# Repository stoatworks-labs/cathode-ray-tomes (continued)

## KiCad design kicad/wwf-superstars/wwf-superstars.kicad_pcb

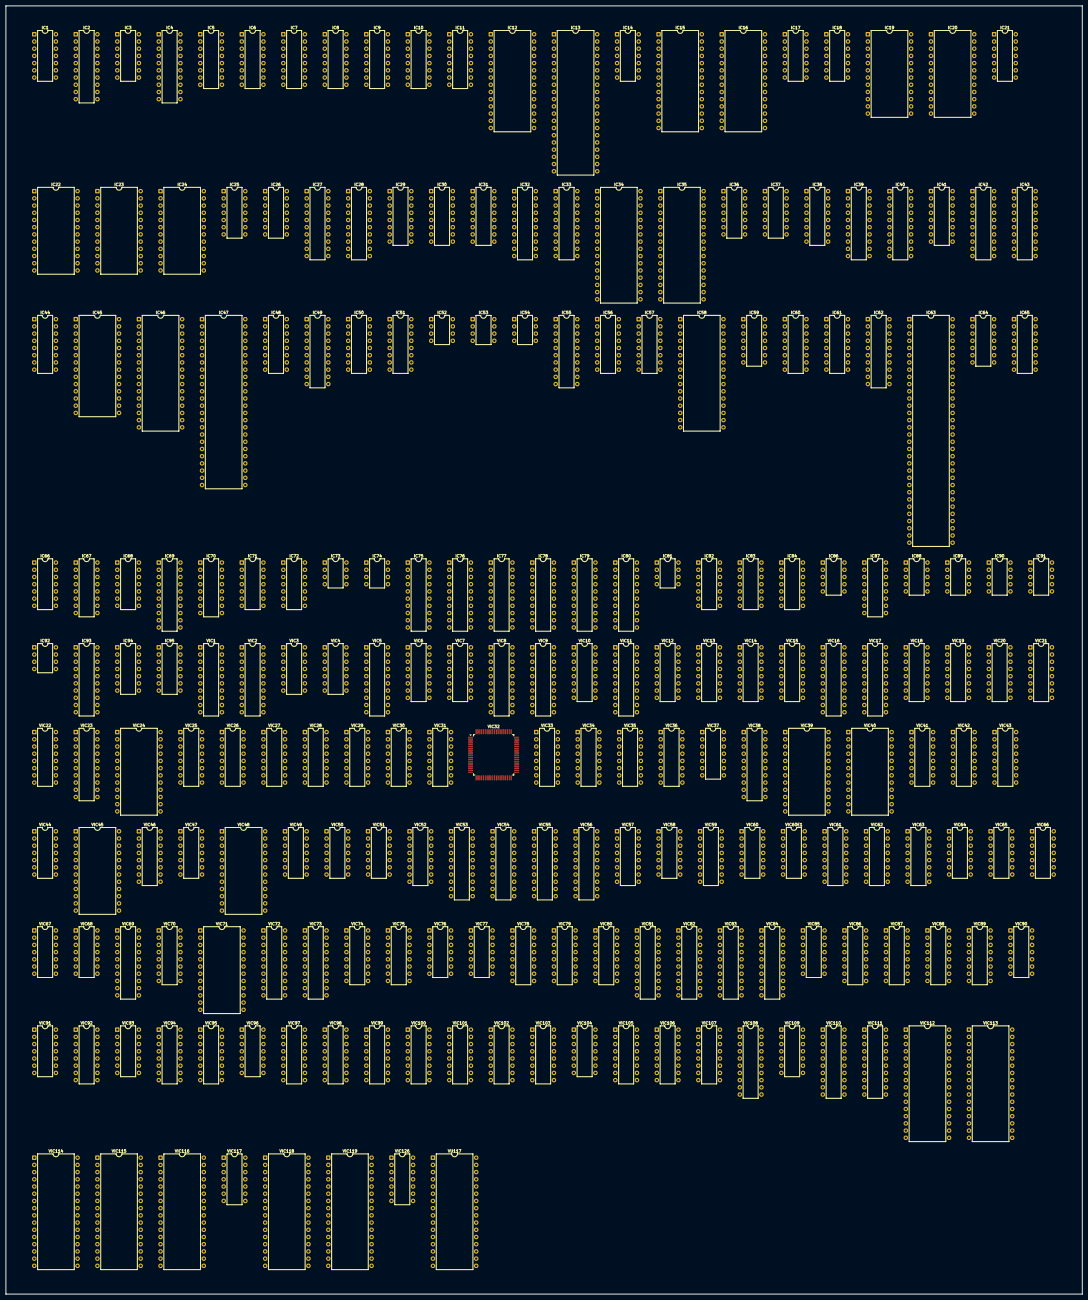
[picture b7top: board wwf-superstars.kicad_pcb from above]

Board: 2 copper layers, 379.2 x 453.8 mm, 216 parts (0 on the bottom side), 913 nets, no tracks yet.

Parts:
IC1, IC37, IC68: 74LS00; DIP-14_W7.62mm
IC2, IC27, IC28, IC32, IC93: 74LS245; DIP-20_W7.62mm
IC3, IC17, IC25, IC95: 74LS10; DIP-14_W7.62mm
IC4, IC39, IC40, IC42, IC43: 74LS273; DIP-20_W7.62mm
IC5, IC6, IC7, IC8, IC29: 74LS153; DIP-16_W7.62mm
IC9, IC10, IC11, IC44, IC56, IC87: 74LS157; DIP-16_W7.62mm
IC12: 27C256; DIP-28_W15.24mm
IC13: Z80CPU; DIP-40_W15.24mm
IC14, IC64, IC72: 74LS04; DIP-14_W7.62mm
IC15, IC16: RAM_2016; DIP-28_W15.24mm
IC18, IC59, IC94: 74LS32; DIP-14_W7.62mm
IC19, IC20, IC22, IC23: RAM_2016; DIP-24_W15.24mm
IC21: 74LS25; DIP-14_W7.62mm
IC24: YM2151; DIP-24_W15.24mm
IC26, IC66, IC71, IC82: 74LS74; DIP-14_W7.62mm
IC30, IC65: 74LS148; DIP-16_W7.62mm
IC31, IC38, IC41, IC67: 74LS174; DIP-16_W7.62mm
IC33, IC55, IC69: 74LS374; DIP-20_W7.62mm
IC34, IC35, IC46, IC58: 27C1000; DIP-32_W15.24mm
IC36: 74LS30; DIP-14_W7.62mm
IC45: 24J8-0; DIP-28_W15.24mm
IC47: OKI6295; DIP-48_W15.24mm
IC48, IC50, IC51, IC60: 74LS138; DIP-16_W7.62mm
IC49, IC62, IC75, IC76, IC77, IC78, IC79, IC80: 74LS244; DIP-20_W7.62mm
IC52: R2R4; DIP-8_W7.62mm
IC53: 74LS374; DIP-8_W7.62mm
IC54: 74AHC273; DIP-8_W7.62mm
IC57, IC70: 74LS194; DIP-16_W7.62mm
IC61: YM3012; DIP-16_W7.62mm
IC63: 68000D; DIP-64_W15.24mm
IC73, IC74, IC81, IC92: HA17558; DIP-8_W7.62mm
IC83: 74LS05; DIP-14_W7.62mm
IC84: 74LS14; DIP-14_W7.62mm
IC86, IC88, IC89, IC90: XXCRXXXX; DIP-10_W7.62mm
IC91: M51516L; DIP-10_W7.62mm
VIC1, VIC2, VIC5, VIC9, VIC11, VIC16, VIC17, VIC38, VIC73, VIC81, VIC82, VIC83, VIC84, VIC108, VIC110, VIC111: 74LS273; DIP-20_W7.62mm
VIC3: 74LS10; DIP-14_W7.62mm
VIC4, VIC37, VIC44, VIC47, VIC49, VIC58, VIC64, VIC77, VIC90, VIC91, VIC96, VIC117: 74LS86; DIP-14_W7.62mm
VIC6, VIC7, VIC21, VIC22, VIC52: 74LS283; DIP-16_W7.62mm
VIC8, VIC23: 74LS245; DIP-20_W7.62mm
VIC10, VIC12, VIC13, VIC14, VIC15, VIC20, VIC25, VIC26, VIC27, VIC34, VIC35, VIC36, VIC41, VIC42, VIC59, VIC70, VIC79, VIC80, VIC87, VIC88, VIC89, VIC105: 74LS157; DIP-16_W7.62mm
VIC18: 74LS367; DIP-16_W7.62mm
VIC19, VIC33, VIC61, VIC62, VIC78, VIC95: 74LS174; DIP-16_W7.62mm
VIC24, VIC39, VIC40, VIC45, VIC48, VIC71: SRAM2K8B; DIP-24_W15.24mm
VIC28, VIC29, VIC30, VIC31: 74LS257; DIP-16_W7.62mm
VIC32: TJ-001; PQFP-80_14x14mm_P0.65mm
VIC43, VIC46, VIC74, VIC75, VIC92, VIC94: 74LS163; DIP-16_W7.62mm
VIC50: 74LS30; DIP-14_W7.62mm
VIC51: 74LS74; DIP-14_W7.62mm
VIC53, VIC55, VIC56, VIC69, VIC72: 74LS374; DIP-20_W7.62mm
VIC54: 74AHC273; DIP-20_W7.62mm
VIC57, VIC63, VIC86: 74LS161; DIP-16_W7.62mm
VIC60, VIC60E1: 74LS08; DIP-14_W7.62mm
VIC65: 74LS32; DIP-14_W7.62mm
VIC66: 74LS00; DIP-14_W7.62mm
VIC67, VIC68, VIC76, VIC126: 74LS04; DIP-14_W7.62mm
VIC85: 74LS27; DIP-14_W7.62mm
VIC93: 74LS02; DIP-14_W7.62mm
VIC97, VIC98, VIC99, VIC100, VIC102, VIC103, VIC106, VIC107: 74LS194; DIP-16_W7.62mm
VIC101: 74LS158; DIP-16_W7.62mm
VIC104: 74LS25; DIP-14_W7.62mm
VIC109: 74LS273; DIP-14_W7.62mm
VIC112: 24J6-0; DIP-32_W15.24mm
VIC113: 24J7-0; DIP-32_W15.24mm
VIC114: TC534000AP; DIP-32_W15.24mm
VIC115, VIC116, VIC118, VIC119: 24J; DIP-32_W15.24mm
VU117: TC534000AP; DIP-32_W15.24mm

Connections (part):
/D~OBJHP0: VIC73.2, VIC74.3, VIC75.3
/D~OBJHP1: VIC73.5, VIC74.4, VIC75.4
/D~OBJHP2: VIC73.6, VIC74.5, VIC75.5
/D~OBJHP3: VIC73.9, VIC74.6, VIC75.6
/D~OBJHP4: VIC46.3, VIC73.12, VIC94.3
/D~OBJHP5: VIC46.4, VIC73.15, VIC94.4
/D~OBJHP6: VIC46.5, VIC73.16, VIC94.5
/D~OBJHP7: VIC46.6, VIC73.19, VIC94.6
/ER0: VIC69.2, VIC71.9, VIC72.3
/ER1: VIC69.5, VIC71.10, VIC72.4
/ER2: VIC69.6, VIC71.11, VIC72.7
/ER3: VIC69.9, VIC71.13, VIC72.8
/ER4: VIC69.12, VIC71.14, VIC72.13
/ER5: VIC69.15, VIC71.15, VIC72.14
/ER6: VIC69.16, VIC71.16, VIC72.17
/ER7: VIC69.19, VIC71.17, VIC72.18
/MA1: IC8.6, IC9.2, IC15.10, IC16.10, IC18.8, IC34.12, IC35.12, IC50.1, IC51.1, IC75.18, VIC12.2, VIC13.2
/MA2: IC8.10, IC9.5, IC15.9, IC16.9, IC34.11, IC35.11, IC50.2, IC51.2, IC75.16, VIC12.5, VIC13.5
/MA3: IC7.6, IC9.11, IC15.8, IC16.8, IC34.10, IC35.10, IC50.3, IC51.3, IC75.14, VIC12.11, VIC13.11
/MA4: IC7.10, IC9.14, IC15.7, IC16.7, IC34.9, IC35.9, IC75.12, VIC12.14, VIC13.14, VIC66.2, VIC66.12
/MA5: IC6.6, IC10.2, IC15.6, IC16.6, IC34.8, IC35.8, IC75.9, VIC25.2, VIC26.2
/MA6: IC6.10, IC10.5, IC15.5, IC16.5, IC34.7, IC35.7, IC75.7, VIC25.5, VIC26.5
/MA7: IC5.6, IC10.11, IC15.4, IC16.4, IC34.6, IC35.6, IC75.5, VIC25.11, VIC26.11
/MA8: IC5.10, IC10.14, IC15.3, IC16.3, IC34.5, IC35.5, IC75.3, VIC25.14, VIC26.14
/MA9: IC11.2, IC15.25, IC16.25, IC29.6, IC34.27, IC35.27, IC62.18, VIC10.2, VIC20.2
/MA10: IC11.5, IC15.24, IC16.24, IC34.26, IC35.26, IC62.16, VIC10.5
/MA11: IC11.11, IC15.21, IC16.21, IC34.23, IC35.23, IC62.14, VIC10.11
/MA12: IC15.23, IC16.23, IC34.25, IC35.25, IC62.12
/MA13: IC15.2, IC16.2, IC34.4, IC35.4, IC62.9
/MA14: IC34.28, IC35.28, IC62.7
/MA15: IC34.29, IC35.29, IC62.5
/MA16: IC34.3, IC35.3, IC62.3
/MD0: IC2.18, IC28.2, IC32.2, IC33.3, IC67.3, IC76.18, IC77.18, IC78.18, IC79.18, IC80.18, VIC8.2
/MD1: IC2.17, IC28.3, IC32.3, IC33.4, IC67.4, IC76.16, IC77.16, IC78.16, IC79.16, IC80.16, VIC8.3
/MD2: IC2.16, IC28.4, IC32.4, IC33.7, IC67.6, IC76.14, IC77.14, IC78.14, IC79.14, IC80.14, VIC8.4
/MD3: IC2.15, IC28.5, IC32.5, IC33.8, IC67.11, IC76.12, IC77.12, IC78.12, IC79.12, IC80.12, VIC8.5
/MD4: IC2.14, IC28.6, IC32.6, IC33.13, IC67.13, IC76.9, IC77.9, IC78.9, IC79.9, VIC8.6
/MD5: IC2.13, IC28.7, IC32.7, IC33.14, IC67.14, IC76.7, IC77.7, IC78.7, IC79.7, VIC8.7
/MD6: IC2.12, IC28.8, IC32.8, IC33.17, IC76.5, IC77.5, IC78.5, IC79.5, VIC8.8
/MD7: IC2.11, IC28.9, IC32.9, IC33.18, IC76.3, IC77.3, IC78.3, IC79.3, VIC8.9
/TEL0: VIC59.2, VIC73.3, VIC111.3
/TEL1: VIC73.4, VIC109.4, VIC111.4
/TEL2: VIC73.7, VIC109.7, VIC111.7
/TEL3: VIC73.8, VIC109.8, VIC111.8
/TEL4: VIC73.13, VIC109.13, VIC111.13
/TEL5: VIC73.14, VIC109.14, VIC111.14
/TEL6: VIC73.17, VIC111.17
/TEL7: VIC73.18, VIC111.18
/bottom/IC4_4: VIC4.4, VIC19.15
/bottom/IC10_6: VIC19.12, VIC51.9
/bottom/IC18_10: VIC18.10, VIC32.6
/bottom/IC18_12: VIC18.12, VIC32.7
/bottom/IC42_10: VIC25.13, VIC32.13, VIC41.11, VIC42.10
/bottom/IC44_1: VIC32.76, VIC32.77, VIC32.80, VIC93.5
/bottom/IC49_12: VIC32.36, VIC49.12
/bottom/IC58_9: VIC64.6, VIC91.3
/bottom/IC59_6: VIC18.2, VIC18.4, VIC32.4, VIC76.1, VIC76.3, VIC76.5
/bottom/IC61_9: VIC32.54, VIC61.9
/bottom/IC62_9: VIC32.60, VIC62.9
/bottom/IC70_3: VIC18.3, VIC32.19, VIC70.3, VIC70.5
/bottom/IC73_11: VIC32.57, VIC73.11
/bottom/IC76_4: VIC51.11, VIC76.4
/bottom/IC82_11: VIC32.65, VIC64.3
/bottom/IC93_2: VIC32.67, VIC32.68, VIC32.69, VIC76.13, VIC89.1, VIC93.2
/bottom/IC110_11: VIC32.58, VIC95.9, VIC108.11, VIC110.11
/bottom/IC111_11: VIC32.55, VIC111.11
/bottom/OROM_~OE: VIC114.24, VU117.24
/bottom/V1: VIC32.43, VIC52.6
/bottom/V2: VIC32.44, VIC52.2
/bottom/V3: VIC32.45, VIC52.15
/bottom/V4: VIC32.46, VIC52.11
/bottom/V5: VIC32.47, VIC34.6
/bottom/V6: VIC32.48, VIC34.2
/bottom/V7: VIC32.49, VIC34.15
/bottom/object/A~CSYNC: VIC13.1, VIC20.1, VIC25.1, VIC68.1
/bottom/object/CHSEQ0: VIC64.9, VIC87.5, VIC88.6
/bottom/object/CODE0: VIC108.2, VIC114.6, VIC115.6, VIC116.6, VIC118.6, VIC119.6, VU117.6
/bottom/object/CODE1: VIC108.5, VIC114.5, VIC115.5, VIC116.5, VIC118.5, VIC119.5, VU117.5
/bottom/object/CODE2: VIC108.6, VIC114.27, VIC115.27, VIC116.27, VIC118.27, VIC119.27, VU117.27
/bottom/object/CODE3: VIC108.9, VIC114.26, VIC115.26, VIC116.26, VIC118.26, VIC119.26, VU117.26
/bottom/object/CODE4: VIC108.12, VIC114.23, VIC115.23, VIC116.23, VIC118.23, VIC119.23, VU117.23
/bottom/object/CODE5: VIC108.15, VIC114.25, VIC115.25, VIC116.25, VIC118.25, VIC119.25, VU117.25
/bottom/object/CODE6: VIC108.16, VIC114.4, VIC115.4, VIC116.4, VIC118.4, VIC119.4, VU117.4
/bottom/object/CODE7: VIC108.19, VIC114.28, VIC115.28, VIC116.28, VIC118.28, VIC119.28, VU117.28
/bottom/object/CODE8: VIC110.2, VIC114.29, VIC115.29, VIC116.29, VIC118.29, VIC119.29, VU117.29
/bottom/object/CODE9: VIC110.5, VIC114.3, VIC115.3, VIC116.3, VIC118.3, VIC119.3, VU117.3
/bottom/object/CODE10: VIC110.6, VIC114.2, VIC116.24, VIC119.24, VU117.2
/bottom/object/CODE11: VIC110.9, VIC114.30, VIC115.1, VIC116.1, VIC118.1, VIC119.1, VU117.30
/bottom/object/CODE12: VIC110.12, VIC114.31, VIC115.22, VIC118.22, VU117.31
/bottom/object/CODE13: VIC110.15, VIC114.22, VIC115.2, VIC116.2, VIC118.2, VIC119.2, VU117.22
/bottom/object/IC19_14: VIC19.14, VIC20.3, VIC41.14, VIC42.13
/bottom/object/IC34_9: VIC34.9, VIC96.2
/bottom/object/IC41_1: VIC41.1, VIC42.1, VIC54.1, VIC56.1, VIC70.1, VIC76.11, VIC87.1, VIC88.1
/bottom/object/IC49_1: VIC25.3, VIC49.1, VIC87.14, VIC88.13
/bottom/object/IC49_4: VIC25.6, VIC41.2, VIC42.3, VIC49.4
/bottom/object/IC49_9: VIC25.10, VIC41.5, VIC42.6, VIC49.9
/bottom/object/IC50_4: VIC34.1, VIC35.5, VIC50.4
/bottom/object/IC50_5: VIC34.13, VIC35.11, VIC50.5
/bottom/object/IC50_6: VIC34.10, VIC35.14, VIC50.6
/bottom/object/IC51_3: VIC35.1, VIC36.1, VIC51.3
/bottom/object/IC59_1: VIC59.1, VIC61.2
/bottom/object/IC61_15: VIC61.15, VIC95.13
/bottom/object/IC62_2: VIC62.2, VIC101.1, VIC105.1
/bottom/object/IC63_1: VIC57.1, VIC63.1, VIC86.1
/bottom/object/IC66_6: VIC57.2, VIC63.2, VIC66.6, VIC70.2, VIC70.6, VIC86.2
/bottom/object/IC66_10: VIC66.10, VIC95.12
/bottom/object/IC68_10: VIC90.9, VIC109.10, VIC117.9
/bottom/object/IC68_12: VIC68.12, VIC90.5, VIC90.10, VIC117.5, VIC117.10
/bottom/object/IC70_4: VIC69.1, VIC70.4, VIC71.21
/bottom/object/IC70_7: VIC40.21, VIC55.1, VIC70.7
/bottom/object/IC76_2: VIC38.11, VIC43.2, VIC46.2, VIC53.11, VIC54.11, VIC56.11, VIC72.11, VIC74.2, VIC75.2, VIC76.2, VIC76.6, VIC92.2, VIC94.2
/bottom/object/IC78_2: VIC78.2, VIC96.4
/bottom/object/IC78_5: VIC78.5, VIC96.9
/bottom/object/IC78_7: VIC78.7, VIC96.12
/bottom/object/IC90_3: VIC90.3, VIC95.11, VIC117.3
/bottom/object/IC91_4: VIC90.2, VIC91.4, VIC96.5, VIC96.10, VIC96.13, VIC111.16, VIC117.2
/bottom/object/IC91_6: VIC59.3, VIC91.6
/bottom/object/M2H: VIC13.3, VIC17.18
/bottom/object/OBJLIN0: VIC90.6, VIC114.8, VIC115.8, VIC116.8, VIC117.6, VIC118.8, VIC119.8, VU117.8
/bottom/object/OBJLIN1: VIC90.8, VIC114.7, VIC115.7, VIC116.7, VIC117.8, VIC118.7, VIC119.7, VU117.7
/bottom/object/OBJVLI0: VIC95.2, VIC114.12, VIC115.12, VIC116.12, VIC118.12, VIC119.12, VU117.12
/bottom/object/OBJVLI1: VIC95.5, VIC114.11, VIC115.11, VIC116.11, VIC118.11, VIC119.11, VU117.11
/bottom/object/OBJVLI2: VIC95.7, VIC114.10, VIC115.10, VIC116.10, VIC118.10, VIC119.10, VU117.10
/bottom/object/OBJVLI3: VIC95.10, VIC114.9, VIC115.9, VIC116.9, VIC118.9, VIC119.9, VU117.9
/bottom/object/V8: VIC14.1, VIC15.1, VIC34.11, VIC60.5
/bottom/object/dual line buffer/03a: VIC18.7, VIC64.1
/bottom/object/dual line buffer/*OBJEI: VIC29.1, VIC31.1
/bottom/object/dual line buffer/CP: VIC18.11, VIC19.9, VIC68.13
/bottom/object/dual line buffer/IC19_4: VIC19.4, VIC49.3
/bottom/object/dual line buffer/IC19_6: VIC19.6, VIC49.6
/bottom/object/dual line buffer/IC19_8: VIC19.11, VIC49.8
/bottom/object/dual line buffer/IC19_11: VIC19.13, VIC49.11
/bottom/object/dual line buffer/IC57_15: VIC63.7, VIC63.10
/bottom/object/dual line buffer/LB0: VIC14.2, VIC14.3
/bottom/object/dual line buffer/LB1: VIC14.5, VIC14.6
/bottom/object/dual line buffer/LB2: VIC14.10, VIC14.11
/bottom/object/dual line buffer/LB4: VIC15.2, VIC15.3
/bottom/object/dual line buffer/LB5: VIC15.5, VIC15.6
/bottom/object/dual line buffer/LB6: VIC15.10, VIC15.11
/bottom/object/dual line buffer/LBA0: VIC16.2, VIC28.3
/bottom/object/dual line buffer/LBA1: VIC16.5, VIC28.6
/bottom/object/dual line buffer/LBA2: VIC16.6, VIC28.10
/bottom/object/dual line buffer/LBA4: VIC16.12, VIC30.3
/bottom/object/dual line buffer/LBA5: VIC16.15, VIC30.6
/bottom/object/dual line buffer/LBA6: VIC16.16, VIC30.10
/bottom/object/dual line buffer/LBB0: VIC17.2, VIC29.3
/bottom/object/dual line buffer/LBB1: VIC17.5, VIC29.6
/bottom/object/dual line buffer/LBB2: VIC17.6, VIC29.10
/bottom/object/dual line buffer/LBB4: VIC17.12, VIC31.3
/bottom/object/dual line buffer/LBB5: VIC17.15, VIC31.6
/bottom/object/dual line buffer/LBB6: VIC17.16, VIC31.10
/bottom/object/dual line buffer/line buffer A/AB0: VIC44.3, VIC45.8
/bottom/object/dual line buffer/line buffer A/AB1: VIC44.6, VIC45.7
/bottom/object/dual line buffer/line buffer A/AB2: VIC44.8, VIC45.6
/bottom/object/dual line buffer/line buffer A/AB3: VIC44.11, VIC45.5
/bottom/object/dual line buffer/line buffer A/AB4: VIC45.4, VIC77.3
/bottom/object/dual line buffer/line buffer A/AB5: VIC45.3, VIC77.6
/bottom/object/dual line buffer/line buffer A/AB6: VIC45.2, VIC77.8
/bottom/object/dual line buffer/line buffer A/AB7: VIC45.1, VIC77.11
/bottom/object/dual line buffer/line buffer A/AB8: VIC45.23, VIC92.14
/bottom/object/dual line buffer/line buffer A/CEP: VIC92.7, VIC94.7
/bottom/object/dual line buffer/line buffer A/CET: VIC75.15, VIC94.10
/bottom/object/dual line buffer/line buffer A/CNT0: VIC44.1, VIC75.14
/bottom/object/dual line buffer/line buffer A/CNT1: VIC44.4, VIC75.13
/bottom/object/dual line buffer/line buffer A/CNT2: VIC44.9, VIC75.12
/bottom/object/dual line buffer/line buffer A/CNT3: VIC44.12, VIC75.11
/bottom/object/dual line buffer/line buffer A/CNT4: VIC77.1, VIC94.14
/bottom/object/dual line buffer/line buffer A/CNT5: VIC77.4, VIC94.13
/bottom/object/dual line buffer/line buffer A/CNT6: VIC77.9, VIC94.12
/bottom/object/dual line buffer/line buffer A/CNT7: VIC77.12, VIC94.11
/bottom/object/dual line buffer/line buffer A/DB0: VIC16.3, VIC28.4, VIC45.9
/bottom/object/dual line buffer/line buffer A/DB1: VIC16.4, VIC28.7, VIC45.10
/bottom/object/dual line buffer/line buffer A/DB2: VIC16.7, VIC28.9, VIC45.11
/bottom/object/dual line buffer/line buffer A/DB3: VIC16.8, VIC28.12, VIC45.13
/bottom/object/dual line buffer/line buffer A/DB4: VIC16.13, VIC30.4, VIC45.14
/bottom/object/dual line buffer/line buffer A/DB5: VIC16.14, VIC30.7, VIC45.15
/bottom/object/dual line buffer/line buffer A/DB6: VIC16.17, VIC30.9, VIC45.16
/bottom/object/dual line buffer/line buffer A/OE1: VIC28.15, VIC30.15, VIC45.21
/bottom/object/dual line buffer/line buffer A/TC: VIC92.10, VIC94.15
/bottom/object/dual line buffer/line buffer A/VCC: VIC16.1, VIC45.24, VIC75.7, VIC75.10
/bottom/object/dual line buffer/line buffer A/VSS: VIC45.12, VIC45.18, VIC45.19, VIC45.20, VIC45.22, VIC89.3, VIC89.6, VIC89.10, VIC89.13, VIC89.15
/bottom/object/dual line buffer/line buffer A/Za: VIC28.2, VIC89.4
/bottom/object/dual line buffer/line buffer A/Zb: VIC28.5, VIC89.7
/bottom/object/dual line buffer/line buffer A/Zc: VIC28.11, VIC89.9
/bottom/object/dual line buffer/line buffer A/Zd: VIC28.14, VIC89.12
/bottom/object/dual line buffer/line buffer A/~MR: VIC75.1, VIC92.1, VIC94.1
/bottom/object/dual line buffer/line buffer A/~PE: VIC75.9, VIC92.9, VIC94.9
/bottom/object/dual line buffer/line buffer B/AB0: VIC48.8, VIC58.3
/bottom/object/dual line buffer/line buffer B/AB1: VIC48.7, VIC58.6
/bottom/object/dual line buffer/line buffer B/AB2: VIC48.6, VIC58.8
/bottom/object/dual line buffer/line buffer B/AB3: VIC48.5, VIC58.11
/bottom/object/dual line buffer/line buffer B/AB4: VIC47.3, VIC48.4
/bottom/object/dual line buffer/line buffer B/AB5: VIC47.6, VIC48.3
/bottom/object/dual line buffer/line buffer B/AB6: VIC47.8, VIC48.2
/bottom/object/dual line buffer/line buffer B/AB7: VIC47.11, VIC48.1
/bottom/object/dual line buffer/line buffer B/AB8: VIC43.14, VIC48.23
/bottom/object/dual line buffer/line buffer B/CEP: VIC43.7, VIC46.7
/bottom/object/dual line buffer/line buffer B/CET: VIC46.10, VIC74.15
/bottom/object/dual line buffer/line buffer B/CNT0: VIC58.1, VIC74.14
/bottom/object/dual line buffer/line buffer B/CNT1: VIC58.4, VIC74.13
/bottom/object/dual line buffer/line buffer B/CNT2: VIC58.9, VIC74.12
/bottom/object/dual line buffer/line buffer B/CNT3: VIC58.12, VIC74.11
/bottom/object/dual line buffer/line buffer B/CNT4: VIC46.14, VIC47.1
/bottom/object/dual line buffer/line buffer B/CNT5: VIC46.13, VIC47.4
/bottom/object/dual line buffer/line buffer B/CNT6: VIC46.12, VIC47.9
/bottom/object/dual line buffer/line buffer B/CNT7: VIC46.11, VIC47.12
/bottom/object/dual line buffer/line buffer B/DB0: VIC17.3, VIC29.4, VIC48.9
/bottom/object/dual line buffer/line buffer B/DB1: VIC17.4, VIC29.7, VIC48.10
/bottom/object/dual line buffer/line buffer B/DB2: VIC17.7, VIC29.9, VIC48.11
/bottom/object/dual line buffer/line buffer B/DB3: VIC17.8, VIC29.12, VIC48.13
/bottom/object/dual line buffer/line buffer B/DB4: VIC17.13, VIC31.4, VIC48.14
/bottom/object/dual line buffer/line buffer B/DB5: VIC17.14, VIC31.7, VIC48.15
/bottom/object/dual line buffer/line buffer B/DB6: VIC17.17, VIC31.9, VIC48.16
/bottom/object/dual line buffer/line buffer B/OE1: VIC29.15, VIC31.15, VIC48.21
/bottom/object/dual line buffer/line buffer B/TC: VIC43.10, VIC46.15
/bottom/object/dual line buffer/line buffer B/VCC: VIC17.1, VIC48.24, VIC74.7, VIC74.10
/bottom/object/dual line buffer/line buffer B/VSS: VIC27.3, VIC27.6, VIC27.10, VIC27.13, VIC27.15, VIC48.12, VIC48.18, VIC48.19, VIC48.20, VIC48.22
/bottom/object/dual line buffer/line buffer B/Za: VIC27.4, VIC29.2
/bottom/object/dual line buffer/line buffer B/Zb: VIC27.7, VIC29.5
/bottom/object/dual line buffer/line buffer B/Zc: VIC27.9, VIC29.11
/bottom/object/dual line buffer/line buffer B/Zd: VIC27.12, VIC29.14
/bottom/object/dual line buffer/line buffer B/~MR: VIC43.1, VIC46.1, VIC74.1
/bottom/object/dual line buffer/line buffer B/~PE: VIC43.9, VIC46.9, VIC74.9
/bottom/object/dual line buffer/~LDS': VIC19.3, VIC64.11
/bottom/object/dual line buffer/~OBJE0: VIC28.1, VIC30.1, VIC60.3
/bottom/object/object RAM/1A2: VIC42.7, VIC71.3
/bottom/object/object RAM/1A3: VIC42.9, VIC71.2
/bottom/object/object RAM/1A4: VIC42.4, VIC42.12, VIC71.1
/bottom/object/object RAM/1C0: VIC13.10, VIC90.12
/bottom/object/object RAM/1C1: VIC13.13, VIC90.13
/bottom/object/object RAM/1Q3: VIC78.10, VIC90.1
/bottom/object/object RAM/A0: VIC40.8, VIC87.4
/bottom/object/object RAM/A1: VIC40.7, VIC87.7
/bottom/object/object RAM/A2: VIC40.6, VIC87.9
/bottom/object/object RAM/A3: VIC40.5, VIC87.12
/bottom/object/object RAM/A4: VIC40.4, VIC41.4
/bottom/object/object RAM/A5: VIC40.3, VIC41.7
/bottom/object/object RAM/A6: VIC40.2, VIC41.9
/bottom/object/object RAM/A7: VIC40.1, VIC41.12
/bottom/object/object RAM/Cp: VIC55.11, VIC69.11
/bottom/object/object RAM/DW0: VIC40.9, VIC55.2, VIC56.3
/bottom/object/object RAM/DW1: VIC40.10, VIC55.5, VIC56.4
/bottom/object/object RAM/DW2: VIC40.11, VIC55.6, VIC56.7
/bottom/object/object RAM/DW3: VIC40.13, VIC55.9, VIC56.8
/bottom/object/object RAM/DW4: VIC40.14, VIC55.12, VIC56.13
/bottom/object/object RAM/DW5: VIC40.15, VIC55.15, VIC56.14
/bottom/object/object RAM/DW6: VIC40.16, VIC55.16, VIC56.17
/bottom/object/object RAM/DW7: VIC40.17, VIC55.19, VIC56.18
/bottom/object/object RAM/F1: VIC54.2, VIC55.3
/bottom/object/object RAM/F2: VIC54.5, VIC55.4
/bottom/object/object RAM/F3: VIC54.6, VIC55.7
/bottom/object/object RAM/F4: VIC54.9, VIC55.8
/bottom/object/object RAM/F5: VIC54.12, VIC55.13
/bottom/object/object RAM/F6: VIC54.15, VIC55.14
/bottom/object/object RAM/F7: VIC54.16, VIC55.17
/bottom/object/object RAM/F8: VIC54.19, VIC55.18
/bottom/object/object RAM/G1: VIC53.2, VIC69.3
/bottom/object/object RAM/G2: VIC53.5, VIC69.4
/bottom/object/object RAM/G3: VIC53.6, VIC69.7
/bottom/object/object RAM/G4: VIC53.9, VIC69.8
/bottom/object/object RAM/G5: VIC53.12, VIC69.13
/bottom/object/object RAM/G6: VIC53.15, VIC69.14
/bottom/object/object RAM/G7: VIC53.16, VIC69.17
/bottom/object/object RAM/G8: VIC53.19, VIC69.18
/bottom/object/object RAM/IC34_4: VIC34.4, VIC35.2
/bottom/object/object RAM/IC42_14: VIC41.13, VIC42.14
/bottom/object/object RAM/IC61_10: VIC61.10, VIC62.6
/bottom/object/object RAM/IC61_12: VIC61.12, VIC62.11
/bottom/object/object RAM/IC62_3: VIC62.3, VIC90.4
/bottom/object/object RAM/IC62_7: VIC61.7, VIC62.4, VIC62.7
/bottom/object/object RAM/IC85_12: VIC57.7, VIC57.10, VIC68.9, VIC85.12
/bottom/object/object RAM/IC88_2: VIC87.3, VIC88.2
/bottom/object/object RAM/IC88_3: VIC87.2, VIC88.3
/bottom/object/object RAM/IC88_5: VIC87.6, VIC88.5
/bottom/object/object RAM/IC88_10: VIC87.11, VIC88.10
/bottom/object/object RAM/IC88_11: VIC87.10, VIC88.11
/bottom/object/object RAM/OA0: VIC13.4, VIC39.8
/bottom/object/object RAM/OA1: VIC13.7, VIC39.7
/bottom/object/object RAM/OA2: VIC13.9, VIC39.6
/bottom/object/object RAM/OA3: VIC13.12, VIC39.5
/bottom/object/object RAM/OA4: VIC25.4, VIC39.4
/bottom/object/object RAM/OA5: VIC25.7, VIC39.3
/bottom/object/object RAM/OA6: VIC25.9, VIC39.2
/bottom/object/object RAM/OA7: VIC25.12, VIC39.1
/bottom/object/object RAM/OB0: VIC8.18, VIC38.3, VIC39.9
/bottom/object/object RAM/OB1: VIC8.17, VIC38.4, VIC39.10
/bottom/object/object RAM/OB2: VIC8.16, VIC38.7, VIC39.11
/bottom/object/object RAM/OB3: VIC8.15, VIC38.8, VIC39.13
/bottom/object/object RAM/OB4: VIC8.14, VIC38.13, VIC39.14
/bottom/object/object RAM/OB5: VIC8.13, VIC38.14, VIC39.15
/bottom/object/object RAM/OB6: VIC8.12, VIC38.17, VIC39.16
/bottom/object/object RAM/OB7: VIC8.11, VIC38.18, VIC39.17
/bottom/object/object RAM/OB8: VIC8.19, VIC66.3
/bottom/object/object RAM/OD0: VIC36.4, VIC53.3, VIC54.3
/bottom/object/object RAM/OD1: VIC36.7, VIC53.4, VIC54.4
/bottom/object/object RAM/OD2: VIC36.9, VIC53.7, VIC54.7
/bottom/object/object RAM/OD3: VIC36.12, VIC53.8, VIC54.8
/bottom/object/object RAM/OD4: VIC35.4, VIC53.13, VIC54.13
/bottom/object/object RAM/OD5: VIC35.7, VIC53.14, VIC54.14
/bottom/object/object RAM/OD6: VIC35.9, VIC53.17, VIC54.17
/bottom/object/object RAM/OD7: VIC35.12, VIC53.18, VIC54.18
/bottom/object/object RAM/OQ0: VIC36.3, VIC38.2, VIC52.5
/bottom/object/object RAM/OQ1: VIC36.6, VIC38.5, VIC52.3
/bottom/object/object RAM/OQ2: VIC36.10, VIC38.6, VIC52.14
/bottom/object/object RAM/OQ3: VIC36.13, VIC38.9, VIC52.12
/bottom/object/object RAM/OQ4: VIC34.5, VIC35.3, VIC38.12
/bottom/object/object RAM/OQ5: VIC34.3, VIC35.6, VIC38.15
/bottom/object/object RAM/OQ6: VIC34.14, VIC35.10, VIC38.16
/bottom/object/object RAM/OQ7: VIC34.12, VIC35.13, VIC38.19
/bottom/object/object RAM/O~WR: VIC20.4, VIC39.23
/bottom/object/object RAM/Q0: VIC57.14, VIC87.13, VIC88.14
/bottom/object/object RAM/Q1: VIC41.3, VIC42.2, VIC57.13, VIC85.13, VIC86.14
/bottom/object/object RAM/Q2: VIC41.6, VIC42.5, VIC57.12, VIC85.2, VIC86.13
/bottom/object/object RAM/Q3: VIC41.10, VIC42.11, VIC57.11
/bottom/object/object RAM/S1: VIC36.2, VIC52.4
/bottom/object/object RAM/S2: VIC36.5, VIC52.1
/bottom/object/object RAM/S3: VIC36.11, VIC52.13
/bottom/object/object RAM/S4: VIC36.14, VIC52.10
/bottom/object/object RAM/TEL0: VIC56.2, VIC61.14, VIC72.2, VIC78.3
/bottom/object/object RAM/TEL1: VIC56.5, VIC61.3, VIC72.5, VIC78.4
/bottom/object/object RAM/TEL2: VIC56.6, VIC72.6, VIC78.6
/bottom/object/object RAM/TEL3: VIC56.9, VIC61.4, VIC72.9, VIC78.11
/bottom/object/object RAM/TEL4: VIC56.12, VIC61.6, VIC72.12, VIC78.13
/bottom/object/object RAM/TEL5: VIC56.15, VIC61.11, VIC72.15
/bottom/object/object RAM/TEL6: VIC56.16, VIC61.13, VIC72.16
/bottom/object/object RAM/TEL7: VIC56.19, VIC72.19
/bottom/object/object RAM/Za: VIC71.8, VIC88.4
/bottom/object/object RAM/Zb: VIC71.7, VIC88.7
/bottom/object/object RAM/Zc: VIC71.6, VIC88.9
/bottom/object/object RAM/Zd: VIC71.5, VIC88.12
/bottom/object/object RAM/~C4: VIC34.7, VIC52.9
/bottom/object/object RAM/~OE: VIC20.7, VIC39.20
/bottom/object/object ROM/CODE_10: VIC115.24, VIC118.24
/bottom/object/object ROM/D0: VIC103.3, VIC115.13, VIC116.13, VU117.13
/bottom/object/object ROM/D1: VIC103.4, VIC115.14, VIC116.14, VU117.14
/bottom/object/object ROM/D2: VIC103.5, VIC115.15, VIC116.15, VU117.15
/bottom/object/object ROM/D3: VIC103.6, VIC115.17, VIC116.17, VU117.17
/bottom/object/object ROM/D4: VIC102.3, VIC115.18, VIC116.18, VU117.18
/bottom/object/object ROM/D5: VIC102.4, VIC115.19, VIC116.19, VU117.19
/bottom/object/object ROM/D6: VIC102.5, VIC115.20, VIC116.20, VU117.20
/bottom/object/object ROM/D7: VIC102.6, VIC115.21, VIC116.21, VU117.21
/bottom/object/object ROM/D8: VIC107.3, VIC114.13, VIC118.13, VIC119.13
/bottom/object/object ROM/D9: VIC107.4, VIC114.14, VIC118.14, VIC119.14
/bottom/object/object ROM/D10: VIC107.5, VIC114.15, VIC118.15, VIC119.15
/bottom/object/object ROM/D11: VIC107.6, VIC114.17, VIC118.17, VIC119.17
/bottom/object/object ROM/D12: VIC106.3, VIC114.18, VIC118.18, VIC119.18
/bottom/object/object ROM/D13: VIC106.4, VIC114.19, VIC118.19, VIC119.19
/bottom/object/object ROM/D14: VIC106.5, VIC114.20, VIC118.20, VIC119.20
/bottom/object/object ROM/D15: VIC106.6, VIC114.21, VIC118.21, VIC119.21
/bottom/object/object ROM/HCLK1: VIC102.11, VIC103.11, VIC106.11, VIC107.11
/bottom/object/object ROM/IC102_12: VIC102.12, VIC105.6
/bottom/object/object ROM/IC102_15: VIC102.15, VIC105.5
/bottom/object/object ROM/IC103_12: VIC103.12, VIC105.3
/bottom/object/object ROM/IC103_15: VIC103.15, VIC105.2
/bottom/object/object ROM/IC106_12: VIC105.13, VIC106.12
/bottom/object/object ROM/IC106_15: VIC105.14, VIC106.15
/bottom/object/object ROM/IC107_12: VIC105.10, VIC107.12
/bottom/object/object ROM/IC107_15: VIC105.11, VIC107.15
/bottom/object/object ROM/OBJCOL_0: VIC104.1, VIC105.4
/bottom/object/object ROM/OBJCOL_1: VIC104.2, VIC105.7
/bottom/object/object ROM/OBJCOL_2: VIC104.4, VIC105.9
/bottom/object/object ROM/OBJCOL_3: VIC104.5, VIC105.12
/bottom/object/object ROM/S0: VIC101.4, VIC102.9, VIC103.9, VIC106.9, VIC107.9
/bottom/object/object ROM/S1: VIC101.7, VIC102.10, VIC103.10, VIC106.10, VIC107.10
/bottom/object/object ROM/VCC: VIC102.1, VIC103.1, VIC104.3, VIC106.1, VIC107.1, VIC114.32, VIC115.32, VIC116.32, VIC118.32, VIC119.32, VU117.32
/bottom/object/object ROM/VSS: VIC101.3, VIC101.5, VIC101.15, VIC102.2, VIC102.7, VIC103.2, VIC103.7, VIC105.15, VIC106.2, VIC106.7, VIC107.2, VIC107.7, VIC114.16, VIC115.16, VIC115.31, VIC116.16, VIC116.31, VIC118.16, VIC118.31, VIC119.16, VIC119.31, VU117.16
/bottom/object/object ROM/~CE: VIC68.2, VIC116.22, VIC119.22
/bottom/scroll/BHP2: VIC3.4, VIC3.10, VIC5.6, VIC37.4, VIC37.10
/bottom/scroll/BHP3: VIC3.13, VIC5.9, VIC37.13
/bottom/scroll/BHP4: VIC3.9, VIC3.12, VIC5.12, VIC12.6
/bottom/scroll/BVP0: VIC6.4, VIC112.12, VIC113.12
/bottom/scroll/BVP1: VIC6.1, VIC112.11, VIC113.11
/bottom/scroll/BVP2: VIC6.13, VIC112.10, VIC113.10
/bottom/scroll/BVP3: VIC6.10, VIC112.9, VIC113.9
/bottom/scroll/CP1: VIC67.8, VIC81.11, VIC83.11
/bottom/scroll/CP2: VIC3.6, VIC33.9, VIC37.6, VIC67.9
/bottom/scroll/IC10_6: VIC10.6, VIC21.11
/bottom/scroll/IC10_10: VIC3.2, VIC3.5
/bottom/scroll/IC37_8: VIC3.8, VIC37.8, VIC112.8, VIC113.8
/bottom/scroll/IC44_1: VIC4.13, VIC37.2
/bottom/scroll/IC58_9: VIC7.2, VIC80.1
/bottom/scroll/IC67_10: VIC67.10, VIC112.7, VIC113.7
/bottom/scroll/IC76_4: VIC5.11, VIC97.11, VIC98.11, VIC99.11, VIC100.11
/bottom/scroll/IC80_4: VIC80.4, VIC97.9, VIC98.9, VIC99.9, VIC100.9
/bottom/scroll/IC80_7: VIC80.7, VIC97.10, VIC98.10, VIC99.10, VIC100.10
/bottom/scroll/IC83_6: VIC83.6, VIC112.24, VIC113.24
/bottom/scroll/IC83_9: VIC83.9, VIC112.1, VIC113.1
/bottom/scroll/IC94_11: VIC10.1, VIC12.1, VIC26.1
/bottom/scroll/MD0: VIC9.3, VIC11.3, VIC23.2
/bottom/scroll/MD1: VIC9.4, VIC11.4, VIC23.3
/bottom/scroll/MD2: VIC9.18, VIC11.7, VIC23.9
/bottom/scroll/MD3: VIC9.17, VIC11.8, VIC23.8
/bottom/scroll/MD4: VIC9.14, VIC11.13, VIC23.7
/bottom/scroll/MD5: VIC9.13, VIC11.14, VIC23.6
/bottom/scroll/MD6: VIC9.8, VIC11.17, VIC23.5
/bottom/scroll/MD7: VIC9.7, VIC11.18, VIC23.4
/bottom/scroll/R~W_VID: VIC10.14, VIC23.1
/bottom/scroll/scroll RAM/1Q7: VIC5.19, VIC12.15, VIC26.3
/bottom/scroll/scroll RAM/A0: VIC12.4, VIC24.8
/bottom/scroll/scroll RAM/A1: VIC12.7, VIC24.7
/bottom/scroll/scroll RAM/A2: VIC12.9, VIC24.6
/bottom/scroll/scroll RAM/A3: VIC12.12, VIC24.5
/bottom/scroll/scroll RAM/A4: VIC24.4, VIC26.4
/bottom/scroll/scroll RAM/A5: VIC24.3, VIC26.7
/bottom/scroll/scroll RAM/A6: VIC24.2, VIC26.9
/bottom/scroll/scroll RAM/A7: VIC24.1, VIC26.12
/bottom/scroll/scroll RAM/A8: VIC10.4, VIC24.23
/bottom/scroll/scroll RAM/A9: VIC10.7, VIC24.22
/bottom/scroll/scroll RAM/A10: VIC10.9, VIC24.19
/bottom/scroll/scroll RAM/A11: VIC10.12, VIC24.20
/bottom/scroll/scroll RAM/ABC: VIC4.8, VIC10.10
/bottom/scroll/scroll RAM/AR2: VIC11.15, VIC22.3
/bottom/scroll/scroll RAM/AR3: VIC11.16, VIC22.14
/bottom/scroll/scroll RAM/AR4: VIC11.19, VIC22.12
/bottom/scroll/scroll RAM/BCG0: VIC81.2, VIC112.6, VIC113.6
/bottom/scroll/scroll RAM/BCG1: VIC81.5, VIC112.5, VIC113.5
/bottom/scroll/scroll RAM/BCG2: VIC81.6, VIC112.27, VIC113.27
/bottom/scroll/scroll RAM/BCG3: VIC81.9, VIC112.26, VIC113.26
/bottom/scroll/scroll RAM/BCG4: VIC81.12, VIC112.23, VIC113.23
/bottom/scroll/scroll RAM/BCG5: VIC81.15, VIC112.25, VIC113.25
/bottom/scroll/scroll RAM/BCG6: VIC81.16, VIC112.4, VIC113.4
/bottom/scroll/scroll RAM/BCG7: VIC81.19, VIC112.28, VIC113.28
/bottom/scroll/scroll RAM/BCG8: VIC83.2, VIC112.29, VIC113.29
/bottom/scroll/scroll RAM/BCG9: VIC83.5, VIC112.3, VIC113.3
/bottom/scroll/scroll RAM/BHP0: VIC4.12, VIC5.2
/bottom/scroll/scroll RAM/BHP5: VIC5.15, VIC12.10
/bottom/scroll/scroll RAM/BHP6: VIC5.16, VIC12.13
/bottom/scroll/scroll RAM/BPL0: VIC33.3, VIC83.12
/bottom/scroll/scroll RAM/BPL1: VIC33.4, VIC83.15
/bottom/scroll/scroll RAM/BPL2: VIC33.6, VIC83.16
/bottom/scroll/scroll RAM/BPL3: VIC33.11, VIC37.9, VIC37.12, VIC83.19
/bottom/scroll/scroll RAM/C0: VIC6.9, VIC22.7
/bottom/scroll/scroll RAM/D0: VIC23.18, VIC24.9, VIC82.3, VIC84.3
/bottom/scroll/scroll RAM/D1: VIC23.17, VIC24.10, VIC82.4, VIC84.4
/bottom/scroll/scroll RAM/D2: VIC23.16, VIC24.11, VIC82.7, VIC84.7
/bottom/scroll/scroll RAM/D3: VIC23.15, VIC24.13, VIC82.8, VIC84.8
/bottom/scroll/scroll RAM/D4: VIC23.14, VIC24.14, VIC82.13, VIC84.13
/bottom/scroll/scroll RAM/D5: VIC23.13, VIC24.15, VIC82.14, VIC84.14
/bottom/scroll/scroll RAM/D6: VIC23.12, VIC24.16, VIC82.17, VIC84.17
/bottom/scroll/scroll RAM/D7: VIC23.11, VIC24.17, VIC82.18, VIC84.18
/bottom/scroll/scroll RAM/DVPAS0: VIC2.2, VIC6.6
/bottom/scroll/scroll RAM/DVPAS1: VIC2.5, VIC6.2
/bottom/scroll/scroll RAM/DVPAS2: VIC2.6, VIC6.15
/bottom/scroll/scroll RAM/DVPAS3: VIC2.9, VIC6.11
/bottom/scroll/scroll RAM/DVPAS4: VIC2.12, VIC22.6
/bottom/scroll/scroll RAM/DVPAS5: VIC2.15, VIC22.2
/bottom/scroll/scroll RAM/DVPAS6: VIC2.16, VIC22.15
/bottom/scroll/scroll RAM/DVPAS7: VIC2.19, VIC22.11
/bottom/scroll/scroll RAM/IC10_3: VIC10.3, VIC21.15, VIC22.10
/bottom/scroll/scroll RAM/IC26_6: VIC22.4, VIC26.6
/bottom/scroll/scroll RAM/IC26_10: VIC22.1, VIC26.10
/bottom/scroll/scroll RAM/IC26_13: VIC22.13, VIC26.13
/bottom/scroll/scroll RAM/Q1: VIC7.5, VIC9.2
/bottom/scroll/scroll RAM/Q2: VIC7.3, VIC9.5
/bottom/scroll/scroll RAM/Q3: VIC7.14, VIC9.6
/bottom/scroll/scroll RAM/Q4: VIC7.12, VIC9.9
/bottom/scroll/scroll RAM/Q5: VIC9.12, VIC21.5
/bottom/scroll/scroll RAM/Q6: VIC9.15, VIC21.3
/bottom/scroll/scroll RAM/Q7: VIC9.16, VIC21.14
/bottom/scroll/scroll RAM/Q8: VIC9.19, VIC21.12
/bottom/scroll/scroll RAM/S1: VIC5.3, VIC7.4
/bottom/scroll/scroll RAM/S2: VIC5.4, VIC7.1
/bottom/scroll/scroll RAM/S3: VIC5.7, VIC7.13
/bottom/scroll/scroll RAM/S4: VIC5.8, VIC7.10
/bottom/scroll/scroll RAM/S5: VIC5.13, VIC21.4
/bottom/scroll/scroll RAM/S6: VIC5.14, VIC21.1
/bottom/scroll/scroll RAM/S7: VIC5.17, VIC21.13
/bottom/scroll/scroll RAM/S8: VIC5.18, VIC21.10
/bottom/scroll/scroll RAM/SA1: VIC11.12, VIC22.5
/bottom/scroll/scroll RAM/VCC: VIC1.1, VIC2.1, VIC5.1, VIC9.1, VIC11.1, VIC24.24, VIC80.3, VIC80.5, VIC81.1, VIC82.1, VIC83.1, VIC84.1
/bottom/scroll/scroll RAM/VSS: VIC6.7, VIC7.7, VIC10.13, VIC10.15, VIC24.12, VIC24.18, VIC26.15, VIC37.1, VIC37.5, VIC80.15
/bottom/scroll/scroll RAM/~C4: VIC7.9, VIC21.7
/bottom/scroll/scroll ROM/PA0: VIC100.3, VIC113.13
/bottom/scroll/scroll ROM/PA1: VIC100.4, VIC113.14
/bottom/scroll/scroll ROM/PA2: VIC100.5, VIC113.15
/bottom/scroll/scroll ROM/PA3: VIC100.6, VIC113.17
/bottom/scroll/scroll ROM/PA4: VIC99.3, VIC113.18
/bottom/scroll/scroll ROM/PA5: VIC99.4, VIC113.19
/bottom/scroll/scroll ROM/PA6: VIC99.5, VIC113.20
/bottom/scroll/scroll ROM/PA7: VIC99.6, VIC113.21
/bottom/scroll/scroll ROM/PB0: VIC98.3, VIC112.13
/bottom/scroll/scroll ROM/PB1: VIC98.4, VIC112.14
/bottom/scroll/scroll ROM/PB2: VIC98.5, VIC112.15
/bottom/scroll/scroll ROM/PB3: VIC98.6, VIC112.17
/bottom/scroll/scroll ROM/PB4: VIC97.3, VIC112.18
/bottom/scroll/scroll ROM/PB5: VIC97.4, VIC112.19
/bottom/scroll/scroll ROM/PB6: VIC97.5, VIC112.20
/bottom/scroll/scroll ROM/PB7: VIC97.6, VIC112.21
/bottom/scroll/scroll ROM/RAW0: VIC79.2, VIC100.15
/bottom/scroll/scroll ROM/RAW3: VIC79.3, VIC100.12
/bottom/scroll/scroll ROM/RAW4: VIC79.5, VIC99.15
/bottom/scroll/scroll ROM/RAW7: VIC79.6, VIC99.12
/bottom/scroll/scroll ROM/RAW8: VIC79.11, VIC98.15
/bottom/scroll/scroll ROM/RAW11: VIC79.10, VIC98.12
/bottom/scroll/scroll ROM/RAW15: VIC79.13, VIC97.12
/bottom/timing/VCC: VIC32.18, VIC32.33, VIC32.38, VIC32.73
/bottom/timing/VSS: VIC32.2, VIC32.12, VIC32.23, VIC32.39, VIC32.40, VIC32.41, VIC32.42, VIC32.52
/top/(-)5V: IC73.4, IC74.4, IC81.4, IC92.4
/top/CHA0: IC43.2, IC58.7
/top/CHA1: IC43.5, IC58.6
/top/CHA2: IC43.6, IC58.5
/top/CHA3: IC43.9, IC58.27
/top/CHA4: IC43.12, IC58.26
/top/CHA5: IC43.15, IC58.23
/top/CHA6: IC43.16, IC58.25
/top/CHA7: IC43.19, IC58.4
/top/CHA8: IC31.2, IC58.28
/top/CHA9: IC31.5, IC58.29
/top/CHA10: IC31.7, IC58.3
/top/CHA11: IC31.10, IC58.2
/top/CHAPXL0: IC6.5, IC8.5, IC21.1, IC40.12
/top/CHAPXL1: IC6.11, IC8.11, IC21.2, IC40.15
/top/CHAPXL2: IC5.5, IC7.5, IC21.4, IC40.16
/top/CHAPXL3: IC7.11, IC21.5, IC40.19
/top/IC14_11: IC14.11, IC26.11, IC82.11
/top/IC25_5: IC25.5, IC49.7, IC64.9
/top/IC28_~CE: IC28.19, IC68.8
/top/IC38_1: IC38.1, IC39.1
/top/IC44_1: IC44.1, IC49.1, IC56.1
/top/IC44_2: IC44.2, IC44.6
/top/IC59_6: IC36.4, IC59.6
/top/IC68_10: IC68.5, IC68.9, IC68.10, IC72.4
/top/LDS: IC1.1, IC17.10, IC37.1, IC64.10, IC68.13, IC69.2
/top/OBJ'0: IC4.2, IC4.12, IC6.4, IC8.4, IC21.9
/top/OBJ'1: IC4.5, IC4.15, IC6.12, IC8.12, IC21.10
/top/OBJ'2: IC4.6, IC4.16, IC5.4, IC7.4, IC21.12
/top/OBJ'3: IC4.9, IC7.12, IC21.13
/top/SCRPXL0: IC6.3, IC8.3
/top/SCRPXL1: IC6.13, IC8.13
/top/SCRPXL2: IC5.3, IC7.3
/top/SLATCH: IC33.11, IC50.11, IC71.3
/top/UDS: IC1.12, IC17.3, IC36.3, IC37.12, IC64.8, IC68.4
/top/V8: IC3.8, IC66.11, IC69.13
/top/char/A0: IC9.4, IC22.8
/top/char/A1: IC9.7, IC22.7
/top/char/A2: IC9.9, IC22.6
/top/char/A3: IC9.12, IC22.5
/top/char/A4: IC10.4, IC22.4
/top/char/A5: IC10.7, IC22.3
/top/char/A6: IC10.9, IC22.2
/top/char/A7: IC10.12, IC22.1
/top/char/A8: IC11.4, IC22.23
/top/char/A9: IC11.7, IC22.22
/top/char/A10: IC11.9, IC22.19
/top/char/D0: IC22.9, IC32.18, IC42.3, IC43.3
/top/char/D1: IC22.10, IC32.17, IC42.4, IC43.4
/top/char/D2: IC22.11, IC32.16, IC42.7, IC43.7
/top/char/D3: IC22.13, IC32.15, IC42.8, IC43.8
/top/char/D4: IC22.14, IC32.14, IC42.13, IC43.13
/top/char/D5: IC22.15, IC32.13, IC42.14, IC43.14
/top/char/D6: IC22.16, IC32.12, IC42.17, IC43.17
/top/char/D7: IC22.17, IC32.11, IC42.18, IC43.18
/top/char/PREPXL0: IC40.13, IC55.12
/top/char/PREPXL1: IC40.14, IC55.15
/top/char/PREPXL2: IC40.17, IC55.16
/top/char/PREPXL3: IC40.18, IC55.19
/top/char/SEL: IC9.1, IC10.1, IC11.1
/top/char/char pixels/PRE0: IC55.2, IC55.13
/top/char/char pixels/PRE1: IC55.5, IC55.14
/top/char/char pixels/PRE2: IC55.6, IC55.17
/top/char/char pixels/PRE3: IC55.9, IC55.18
/top/char/char pixels/PXLA0: IC56.2, IC57.15
/top/char/char pixels/PXLA1: IC56.5, IC57.13
/top/char/char pixels/PXLA2: IC56.11, IC70.15
/top/char/char pixels/PXLA3: IC56.14, IC70.13
/top/char/char pixels/PXLB0: IC56.3, IC57.14
/top/char/char pixels/PXLB1: IC56.6, IC57.12
/top/char/char pixels/PXLB2: IC56.10, IC70.14
/top/char/char pixels/PXLB3: IC56.13, IC70.12
/top/char/char pixels/S0: IC44.4, IC57.9, IC70.9
/top/char/char pixels/S1: IC44.7, IC57.10, IC70.10
/top/char/char pixels/VCC: IC44.3, IC44.5, IC55.1, IC55.20, IC57.1, IC57.16, IC58.1, IC58.31, IC58.32, IC70.1, IC70.16
/top/char/char pixels/VSS: IC44.15, IC55.10, IC56.15, IC57.2, IC57.7, IC57.8, IC58.16, IC58.22, IC58.24, IC70.2, IC70.7, IC70.8
/top/char/char pixels/~CHSEQ2: IC55.11, IC57.11, IC70.11
/top/char/~CHSEQ0: IC9.3, IC41.9, IC42.11
/top/char/~CHSEQ1: IC31.9, IC43.11
/top/char/~MCHAR: IC32.19, IC68.11
/top/char/~PRECHDTACK: IC26.8, IC40.8
/top/char/~RAMOE: IC11.12, IC22.20
/top/char/~RAMWE: IC22.21, IC69.12
/top/color mixer/B0: IC38.10, IC52.2
/top/color mixer/B1: IC38.7, IC52.3
/top/color mixer/B2: IC38.5, IC52.4
/top/color mixer/B3: IC38.2, IC52.5
/top/color mixer/COLMIXS0: IC5.14, IC6.14, IC7.14, IC8.14, IC29.14, IC30.7
/top/color mixer/COLMIXS1: IC5.2, IC6.2, IC7.2, IC8.2, IC29.2, IC30.9
/top/color mixer/G0: IC39.19, IC53.2
/top/color mixer/G1: IC39.16, IC53.3
/top/color mixer/G2: IC39.15, IC53.4
/top/color mixer/G3: IC39.12, IC53.5
/top/color mixer/PD0: IC19.9, IC28.18
/top/color mixer/PD1: IC19.10, IC28.17
/top/color mixer/PD2: IC19.11, IC28.16
/top/color mixer/PD3: IC19.13, IC28.15
/top/color mixer/PD4: IC19.14, IC28.14
/top/color mixer/PD5: IC19.15, IC28.13
/top/color mixer/PD6: IC19.16, IC28.12
/top/color mixer/PD7: IC19.17, IC28.11
/top/color mixer/PD8: IC20.9, IC27.18
/top/color mixer/PD9: IC20.10, IC27.17
/top/color mixer/PD10: IC20.11, IC27.16
/top/color mixer/PD11: IC20.13, IC27.15
/top/color mixer/PD12: IC20.14, IC27.14
/top/color mixer/PD13: IC20.15, IC27.13
/top/color mixer/PD14: IC20.16, IC27.12
/top/color mixer/PD15: IC20.17, IC27.11
/top/color mixer/R0: IC39.9, IC54.2
/top/color mixer/R1: IC39.6, IC54.3
/top/color mixer/R2: IC39.5, IC54.4
/top/color mixer/R3: IC39.2, IC54.5
/top/color mixer/RA0: IC8.7, IC19.8, IC20.8
/top/color mixer/RA1: IC8.9, IC19.7, IC20.7
/top/color mixer/RA2: IC7.7, IC19.6, IC20.6
/top/color mixer/RA3: IC7.9, IC19.5, IC20.5
/top/color mixer/RA4: IC6.7, IC19.4, IC20.4
/top/color mixer/RA5: IC6.9, IC19.3, IC20.3
/top/color mixer/RA6: IC5.7, IC19.2, IC20.2
/top/color mixer/RA7: IC5.9, IC19.1, IC20.1
/top/color mixer/RA8: IC19.23, IC20.23, IC29.7
/top/color mixer/~CHOPAQ: IC21.6, IC30.3
/top/color mixer/~OBJOPAQ: IC21.8, IC30.2
/top/io/1P_BTN_1': IC79.11, IC88.3
/top/io/1P_BTN_2': IC79.13, IC88.5
/top/io/1P_BTN_3': IC79.15, IC88.7
/top/io/1P_DOWN': IC79.8, IC89.9
/top/io/1P_LEFT': IC79.4, IC89.5
/top/io/1P_RIGHT': IC79.2, IC89.3
/top/io/1P_START': IC79.17, IC88.9
/top/io/1P_UP': IC79.6, IC89.7
/top/io/2P_BTN_3': IC78.15, IC86.7
/top/io/2P_DOWN': IC78.8, IC87.12
/top/io/2P_LEFT': IC78.4, IC87.7
/top/io/2P_RIGHT': IC78.2, IC87.4
/top/io/2P_START': IC78.17, IC86.9
/top/io/2P_UP': IC78.6, IC87.9
/top/io/COIN1': IC80.4, IC84.11, IC90.3
/top/io/COIN2': IC80.6, IC84.9, IC90.5
/top/io/SERVICE': IC80.8, IC90.7
/top/io/~2P_BTN_1': IC78.11, IC86.3
/top/io/~2P_BTN_2': IC78.13, IC86.5
/top/io/~PLYR1: IC51.13, IC79.1, IC79.19
/top/io/~PLYR2: IC51.12, IC78.1, IC78.19
/top/io/~SW1: IC51.15, IC77.1, IC77.19
/top/io/~SW2: IC51.14, IC76.1, IC76.19
/top/io/~SYS: IC51.11, IC80.1
/top/main/A1: IC63.29, IC75.2
/top/main/A2: IC63.30, IC75.4
/top/main/A3: IC63.31, IC75.6
/top/main/A4: IC63.32, IC75.8
/top/main/A5: IC63.33, IC75.11
/top/main/A6: IC63.34, IC75.13
/top/main/A7: IC63.35, IC75.15
/top/main/A8: IC63.36, IC75.17
/top/main/A9: IC62.2, IC63.37
/top/main/A10: IC62.4, IC63.38
/top/main/A11: IC62.6, IC63.39
/top/main/A12: IC62.8, IC63.40
/top/main/A13: IC62.11, IC63.41
/top/main/A14: IC62.13, IC63.42
/top/main/A15: IC62.15, IC63.43
/top/main/A16: IC62.17, IC63.44
/top/main/A17: IC34.2, IC35.2, IC63.45
/top/main/A18: IC48.1, IC63.46
/top/main/A19: IC48.2, IC63.47
/top/main/A20: IC48.3, IC63.48
/top/main/CLK: IC63.15, IC82.2, IC82.6
/top/main/D0: IC2.2, IC16.11, IC35.13, IC63.5
/top/main/D1: IC2.3, IC16.12, IC35.14, IC63.4
/top/main/D2: IC2.4, IC16.13, IC35.15, IC63.3
/top/main/D3: IC2.5, IC16.15, IC35.17, IC63.2
/top/main/D4: IC2.6, IC16.16, IC35.18, IC63.1
/top/main/D5: IC2.7, IC16.17, IC35.19, IC63.64
/top/main/D6: IC2.8, IC16.18, IC35.20, IC63.63
/top/main/D7: IC2.9, IC16.19, IC35.21, IC63.62
/top/main/D8: IC15.11, IC34.13, IC63.61, IC93.9
/top/main/D9: IC15.12, IC34.14, IC63.60, IC93.8
/top/main/D10: IC15.13, IC34.15, IC63.59, IC93.7
/top/main/D11: IC15.15, IC34.17, IC63.58, IC93.6
/top/main/D12: IC15.16, IC34.18, IC63.57, IC93.5
/top/main/D13: IC15.17, IC34.19, IC63.56, IC93.4
/top/main/D14: IC15.18, IC34.20, IC63.55, IC93.3
/top/main/D15: IC15.19, IC34.21, IC63.54, IC93.2
/top/main/FC0: IC25.9, IC63.28
/top/main/FC1: IC25.10, IC63.27
/top/main/FC2: IC25.11, IC63.26
/top/main/R~W: IC49.11, IC63.9
/top/main/R~WB: IC25.3, IC37.2, IC37.13, IC49.9, IC64.3, IC64.5
/top/main/VPA: IC3.2, IC18.3, IC63.21
/top/main/~DTACK: IC37.8, IC63.10
/top/main/~IRQ5_CLR: IC50.14, IC66.13
/top/main/~IRQ6_CLR: IC50.15, IC66.1
/top/main/~LDR: IC16.22, IC35.24, IC37.3
/top/main/~LDS': IC25.4, IC49.5, IC50.5, IC64.11
/top/main/~LDS: IC49.15, IC63.8
/top/main/~LDW: IC1.3, IC16.27
/top/main/~OBJ: IC48.11, IC59.4
/top/main/~PAL: IC48.10, IC59.9
/top/main/~RAM: IC15.20, IC16.20, IC17.4, IC17.11, IC48.7
/top/main/~ROM: IC17.5, IC17.9, IC18.12, IC34.22, IC35.22, IC36.5, IC48.15
/top/main/~UDR: IC15.22, IC34.24, IC37.11
/top/main/~UDS: IC49.13, IC63.7
/top/main/~UDW: IC1.11, IC15.27
/top/sound/A0: IC12.10, IC13.30, IC23.8, IC24.4
/top/sound/A1: IC12.9, IC13.31, IC23.7
/top/sound/A2: IC12.8, IC13.32, IC23.6
/top/sound/A3: IC12.7, IC13.33, IC23.5
/top/sound/A4: IC12.6, IC13.34, IC23.4
/top/sound/A5: IC12.5, IC13.35, IC23.3
/top/sound/A6: IC12.4, IC13.36, IC23.2
/top/sound/A7: IC12.3, IC13.37, IC23.1
/top/sound/A8: IC12.25, IC13.38, IC23.23
/top/sound/A9: IC12.24, IC13.39, IC23.22
/top/sound/A10: IC12.21, IC13.40, IC23.19
/top/sound/A11: IC12.23, IC13.1, IC60.1
/top/sound/A12: IC12.2, IC13.2, IC60.2
/top/sound/A13: IC12.26, IC13.3, IC60.3
/top/sound/A14: IC12.27, IC13.4, IC60.4
/top/sound/A15: IC12.20, IC13.5, IC60.6
/top/sound/D0: IC12.11, IC13.14, IC23.9, IC24.10, IC33.2, IC47.37
/top/sound/D1: IC12.12, IC13.15, IC23.10, IC24.12, IC33.5, IC47.38
/top/sound/D2: IC12.13, IC13.12, IC23.11, IC24.13, IC33.6, IC47.39
/top/sound/D3: IC12.15, IC13.8, IC23.13, IC24.14, IC33.9, IC47.40
/top/sound/D4: IC12.16, IC13.7, IC23.14, IC24.15, IC33.12, IC47.41
/top/sound/D5: IC12.17, IC13.9, IC23.15, IC24.16, IC33.15, IC47.42
/top/sound/D6: IC12.18, IC13.10, IC23.16, IC24.17, IC33.16, IC47.43
/top/sound/D7: IC12.19, IC13.13, IC23.17, IC24.18, IC33.19, IC47.44
/top/sound/IC24_19: IC24.19, IC61.5
/top/sound/IC24_20: IC24.20, IC61.6
/top/sound/IC24_21: IC24.21, IC61.4
/top/sound/IC24_23: IC24.23, IC61.2
/top/sound/PA0: IC45.10, IC46.12, IC47.18
/top/sound/PA1: IC45.9, IC46.11, IC47.19
/top/sound/PA2: IC45.8, IC46.10, IC47.20
/top/sound/PA3: IC45.7, IC46.9, IC47.21
/top/sound/PA4: IC45.6, IC46.8, IC47.22
/top/sound/PA5: IC45.5, IC46.7, IC47.23
/top/sound/PA6: IC45.4, IC46.6, IC47.24
/top/sound/PA7: IC45.3, IC46.5, IC47.25
/top/sound/PA8: IC45.25, IC46.27, IC47.26
/top/sound/PA9: IC45.24, IC46.26, IC47.27
/top/sound/PA10: IC45.21, IC46.23, IC47.28
/top/sound/PA11: IC45.23, IC46.25, IC47.29
/top/sound/PA12: IC45.2, IC46.4, IC47.30
/top/sound/PA13: IC45.26, IC46.28, IC47.31
/top/sound/PA14: IC45.27, IC46.29, IC47.32
/top/sound/PA15: IC45.1, IC46.3, IC47.33
/top/sound/PA16: IC45.22, IC46.24, IC47.34
/top/sound/PA17: IC46.22, IC47.35
/top/sound/PD0: IC45.11, IC46.13, IC47.9
/top/sound/PD1: IC45.12, IC46.14, IC47.10
/top/sound/PD2: IC45.13, IC46.15, IC47.11
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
